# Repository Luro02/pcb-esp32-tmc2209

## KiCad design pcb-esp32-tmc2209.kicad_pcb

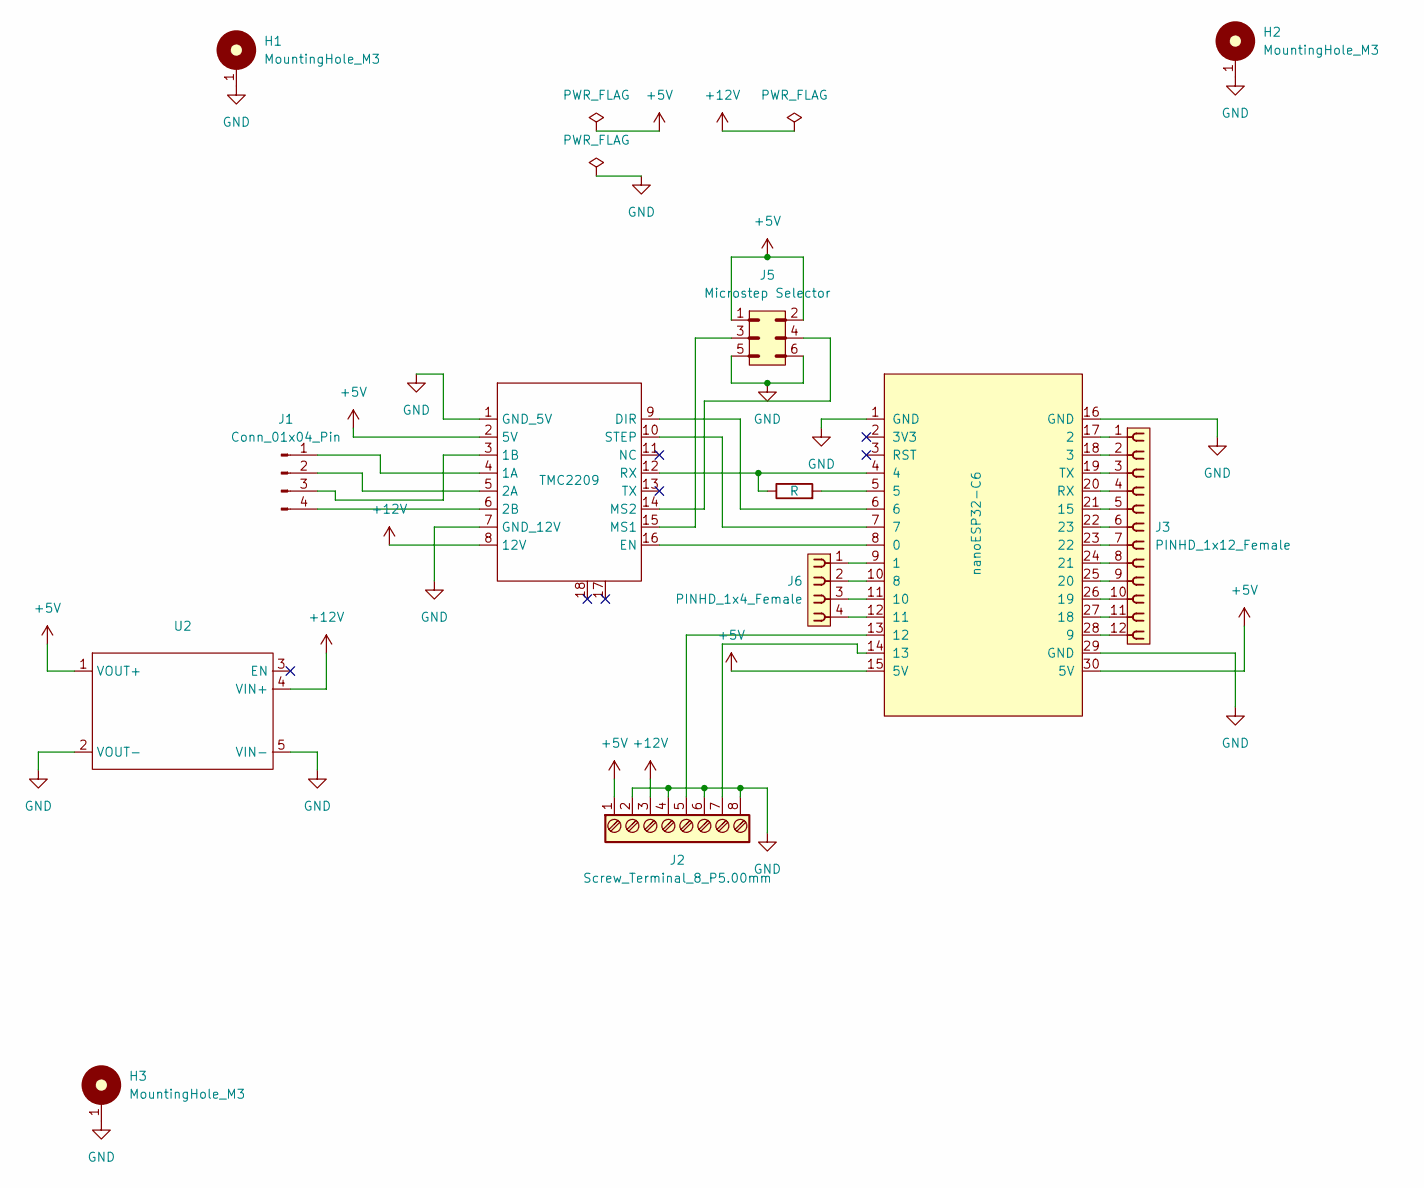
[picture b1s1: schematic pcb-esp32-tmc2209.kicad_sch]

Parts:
H1, H2, H3: MountingHole_M3; MountingHole_3.2mm_Pad
J1: Conn_01x04_Pin; PinHeader_1x04_P2.54mm_Vertical
J2: Screw_Terminal_8_P5.00mm; TerminalBlock_bornier-8_P5.08mm
J3: PINHD_1x12_Female; PinSocket_1x12_P2.54mm_Vertical
J5: Microstep Selector; PinHeader_2x03_P2.54mm_Vertical
J6: PINHD_1x4_Female; PinSocket_1x04_P2.54mm_Vertical
R1: R; R_Axial_DIN0207_L6.3mm_D2.5mm_P10.16mm_Horizontal
TMC2209: TMC2209
U1: nanoESP32-C6
U2: V100-EY9 DC-DC Converter

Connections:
+5V: J2.1, J5.1, J5.2, TMC2209.2 (5V), U1.15 (5V), U1.30 (5V), U2.1 (VOUT+)
+12V: J2.3, TMC2209.8 (12V), U2.4 (VIN+)
GND: H1.1, H2.1, H3.1, J2.2, J2.4, J2.6, J2.8, J5.5, J5.6, TMC2209.1 (GND_5V), TMC2209.7 (GND_12V), U1.1 (GND), U1.16 (GND), U1.29 (GND), U2.2 (VOUT-), U2.5 (VIN-)
unnamed: J1.1, TMC2209.4 (1A)
unnamed: J1.2, TMC2209.5 (2A)
unnamed: J1.3, TMC2209.3 (1B)
unnamed: J1.4, TMC2209.6 (2B)
unnamed: R1.2, U1.5
unnamed: TMC2209.9 (DIR), U1.6
unnamed: TMC2209.16 (EN), U1.8 (0)
unnamed: J5.3, TMC2209.15 (MS1)
unnamed: J5.4, TMC2209.14 (MS2)
unnamed: R1.1, TMC2209.12 (RX), U1.4
unnamed: TMC2209.10 (STEP), U1.7
unnamed: J6.1, U1.9 (1)
unnamed: J3.1, U1.17 (2)
unnamed: J3.2, U1.18 (3)
unnamed: J6.2, U1.10 (8)
unnamed: J3.12, U1.28 (9)
unnamed: J6.3, U1.11 (10)
unnamed: J6.4, U1.12 (11)
unnamed: J2.5, U1.13 (12)
unnamed: J2.7, U1.14 (13)
unnamed: J3.5, U1.21 (15)
unnamed: J3.11, U1.27 (18)
unnamed: J3.10, U1.26 (19)
unnamed: J3.9, U1.25 (20)
unnamed: J3.8, U1.24 (21)
unnamed: J3.7, U1.23 (22)
unnamed: J3.6, U1.22 (23)
unnamed: J3.4, U1.20 (RX)
unnamed: J3.3, U1.19 (TX)

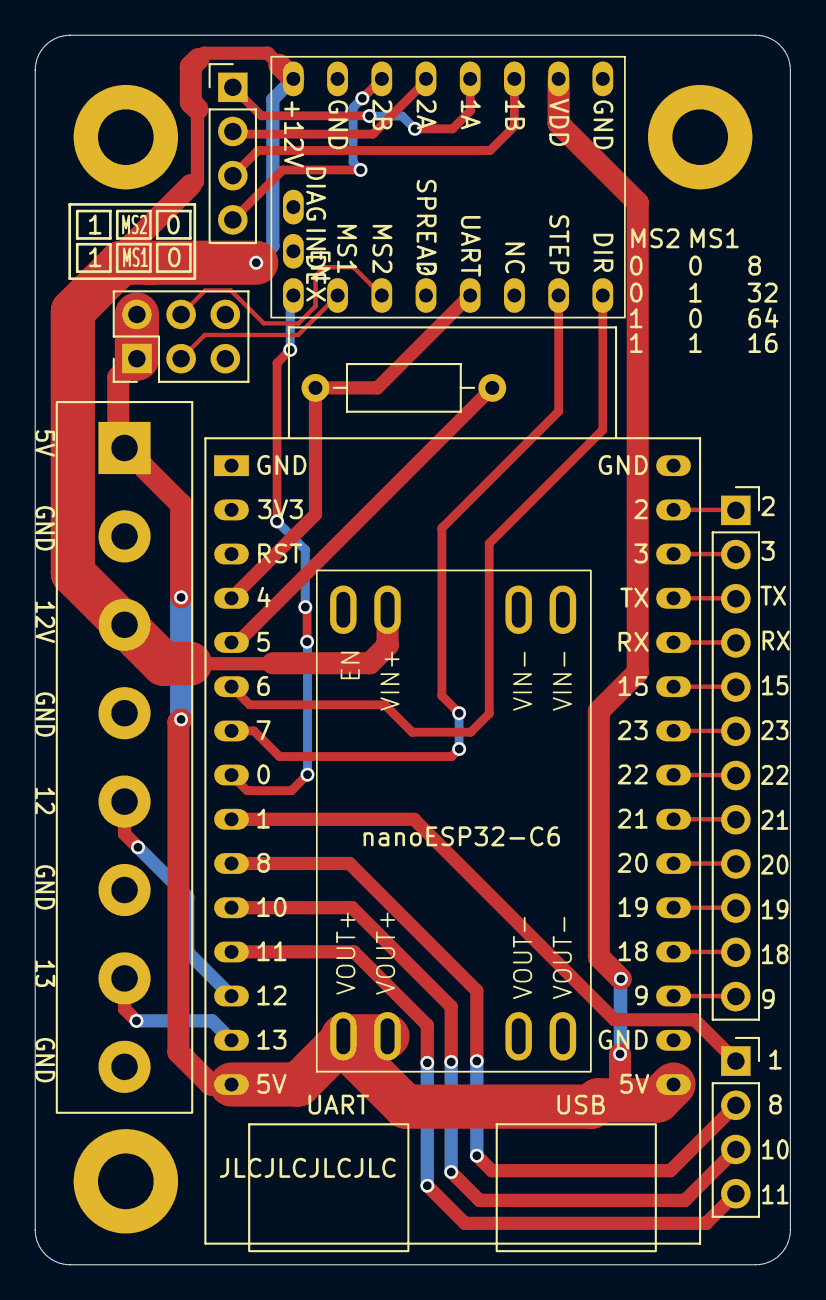
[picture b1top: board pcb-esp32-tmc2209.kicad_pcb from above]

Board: 2 copper layers, 43.4 x 70.7 mm, 12 parts (0 on the bottom side), 32 nets.

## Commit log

2024-05-11 add components
2024-05-11 run ci on every push
2024-05-11 fix ci warnings?
2024-05-11 include drill files
2024-05-11 export drill files to separate dir
2024-08-19 initial commit of version 2
